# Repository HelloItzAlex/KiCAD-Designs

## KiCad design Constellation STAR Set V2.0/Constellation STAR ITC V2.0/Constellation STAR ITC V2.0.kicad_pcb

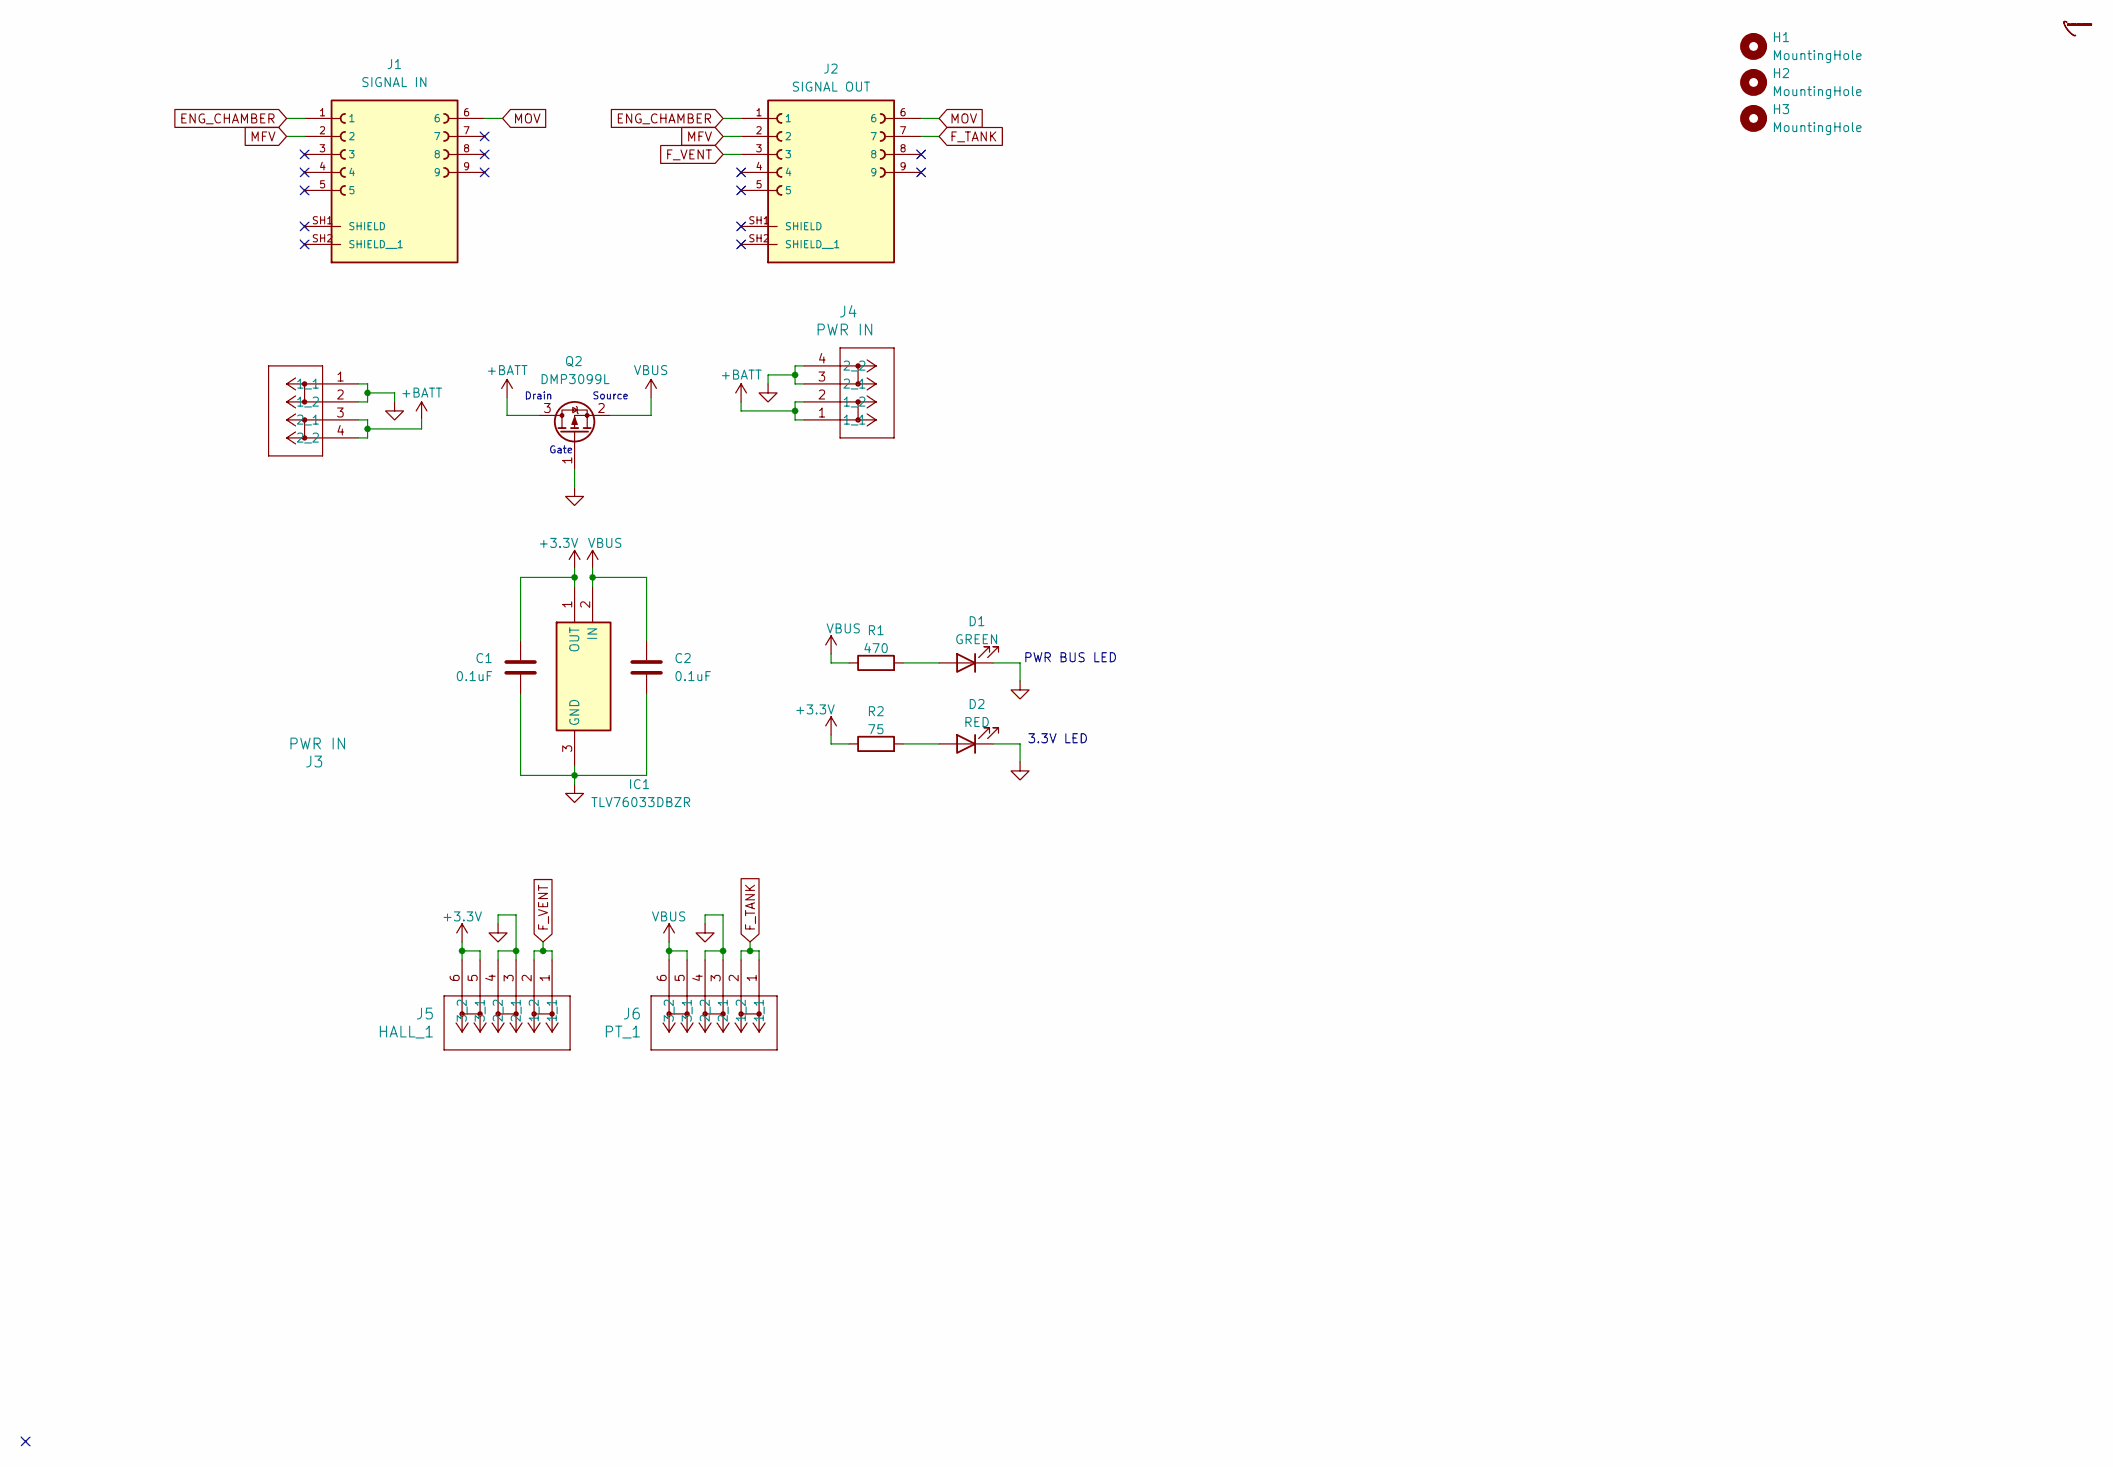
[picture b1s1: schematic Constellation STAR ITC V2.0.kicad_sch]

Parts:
C1, C2: 0.1uF; C_0805_2012Metric
D1: GREEN; LED_0805_2012Metric
D2: RED; LED_0805_2012Metric
H1, H2, H3: MountingHole; MountingHole_3.2mm_M3
IC1: TLV76033DBZR; SOT95P237X112-3N; Mouser Part Number 595-TLV76033DBZR
J1: SIGNAL IN; AMPHENOL_LD09S33E4GV00LF; PARTREV B
J2: SIGNAL OUT; AMPHENOL_LD09S33E4GV00LF; PARTREV B
J3, J4: PWR IN; CONN2_2601-1102_WAG
J5: HALL_1; CONN3_2601-1103_WAG
J6: PT_1; CONN3_2601-1103_WAG
Q2: DMP3099L; SOT-23-3
R1: 470; R_0805_2012Metric
R2: 75; R_0805_2012Metric

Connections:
+3.3V: C1.1, IC1.1 (OUT), J5.5 (3_1), J5.6 (3_2), R2.1
+BATT: J3.3 (2_1), J3.4 (2_2), J4.1 (1_1), J4.2 (1_2), Q2.3 (D)
ENG_CHAMBER: J1.1, J2.1
F_TANK: J2.7, J6.1 (1_1), J6.2 (1_2)
F_VENT: J2.3, J5.1 (1_1), J5.2 (1_2)
GND: C1.2, C2.2, D1.1 (K), D2.1 (K), IC1.3 (GND), J3.1 (1_1), J3.2 (1_2), J4.3 (2_1), J4.4 (2_2), J5.3 (2_1), J5.4 (2_2), J6.3 (2_1), J6.4 (2_2), Q2.1 (G)
MFV: J1.2, J2.2
MOV: J1.6, J2.6
unnamed: D1.2 (A), R1.2
unnamed: D2.2 (A), R2.2
VBUS: C2.1, IC1.2 (IN), J6.5 (3_1), J6.6 (3_2), Q2.2 (S), R1.1

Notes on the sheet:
PWR BUS LED
Source
Gate
Drain
3.3V LED

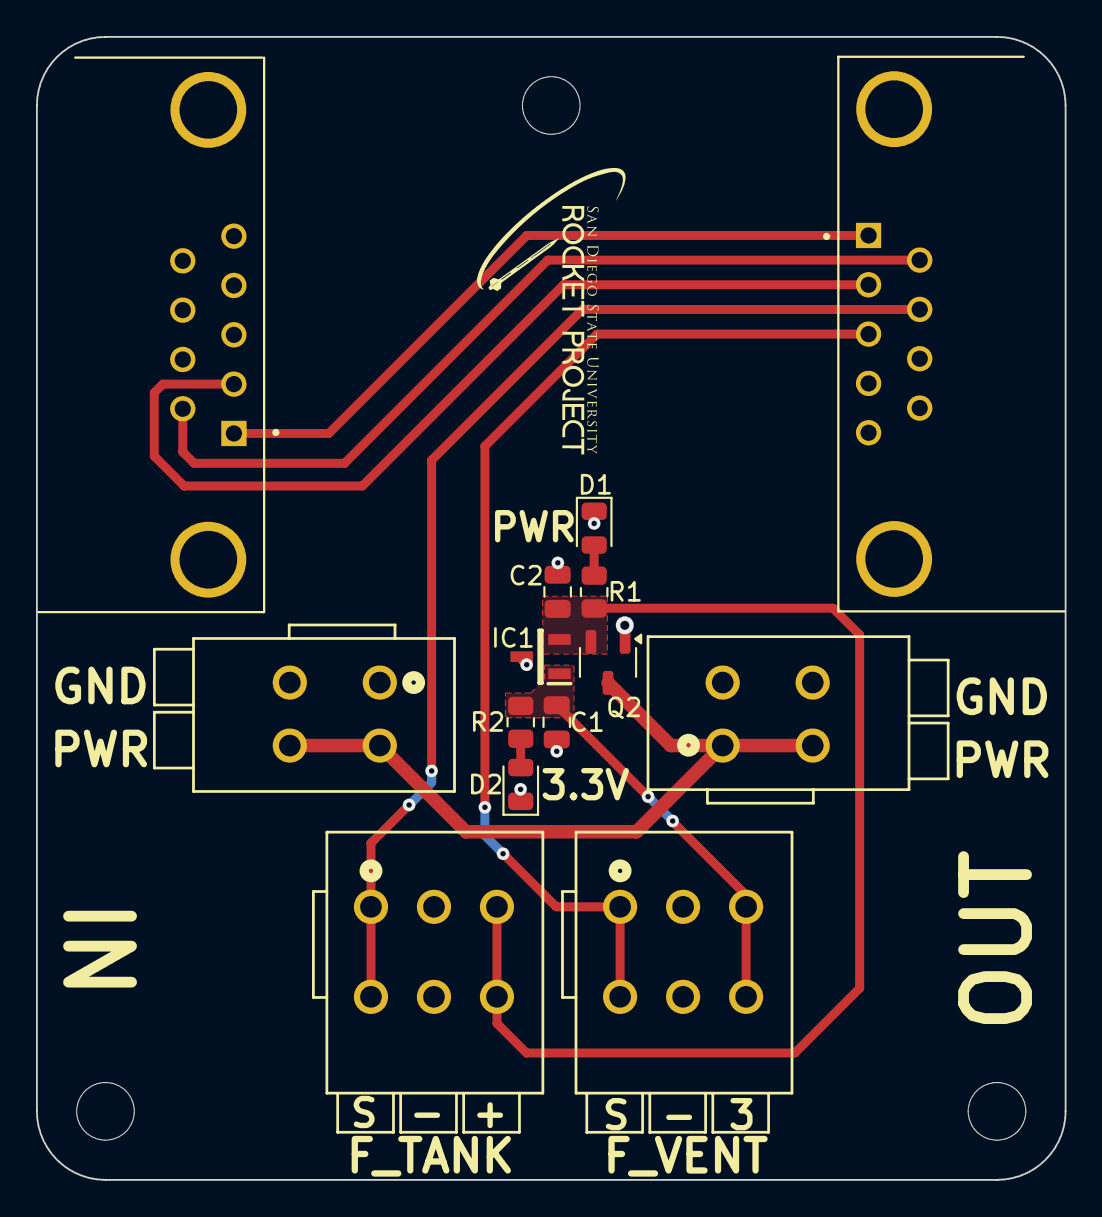
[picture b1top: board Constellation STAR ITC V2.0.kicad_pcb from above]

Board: 2 copper layers, 57.1 x 63.5 mm, 17 parts (0 on the bottom side), 11 nets.

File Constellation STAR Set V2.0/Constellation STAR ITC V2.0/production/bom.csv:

Designator,Footprint,Quantity,Value,LCSC Part #
"C1, C2",0805,2,0.1uF,
D1,0805,1,GREEN,
D2,0805,1,RED,
IC1,SOT95P237X112-3N,1,TLV76033DBZR,
J1,AMPHENOL_LD09S33E4GV00LF,1,SIGNAL IN,
J2,AMPHENOL_LD09S33E4GV00LF,1,SIGNAL OUT,
"J3, J4",CONN2_2601-1102_WAG,2,PWR IN,
J5,CONN3_2601-1103_WAG,1,HALL_1,
J6,CONN3_2601-1103_WAG,1,PT_1,
Q2,SOT-23-3,1,DMP3099L,
R1,0805,1,470,
R2,0805,1,75,

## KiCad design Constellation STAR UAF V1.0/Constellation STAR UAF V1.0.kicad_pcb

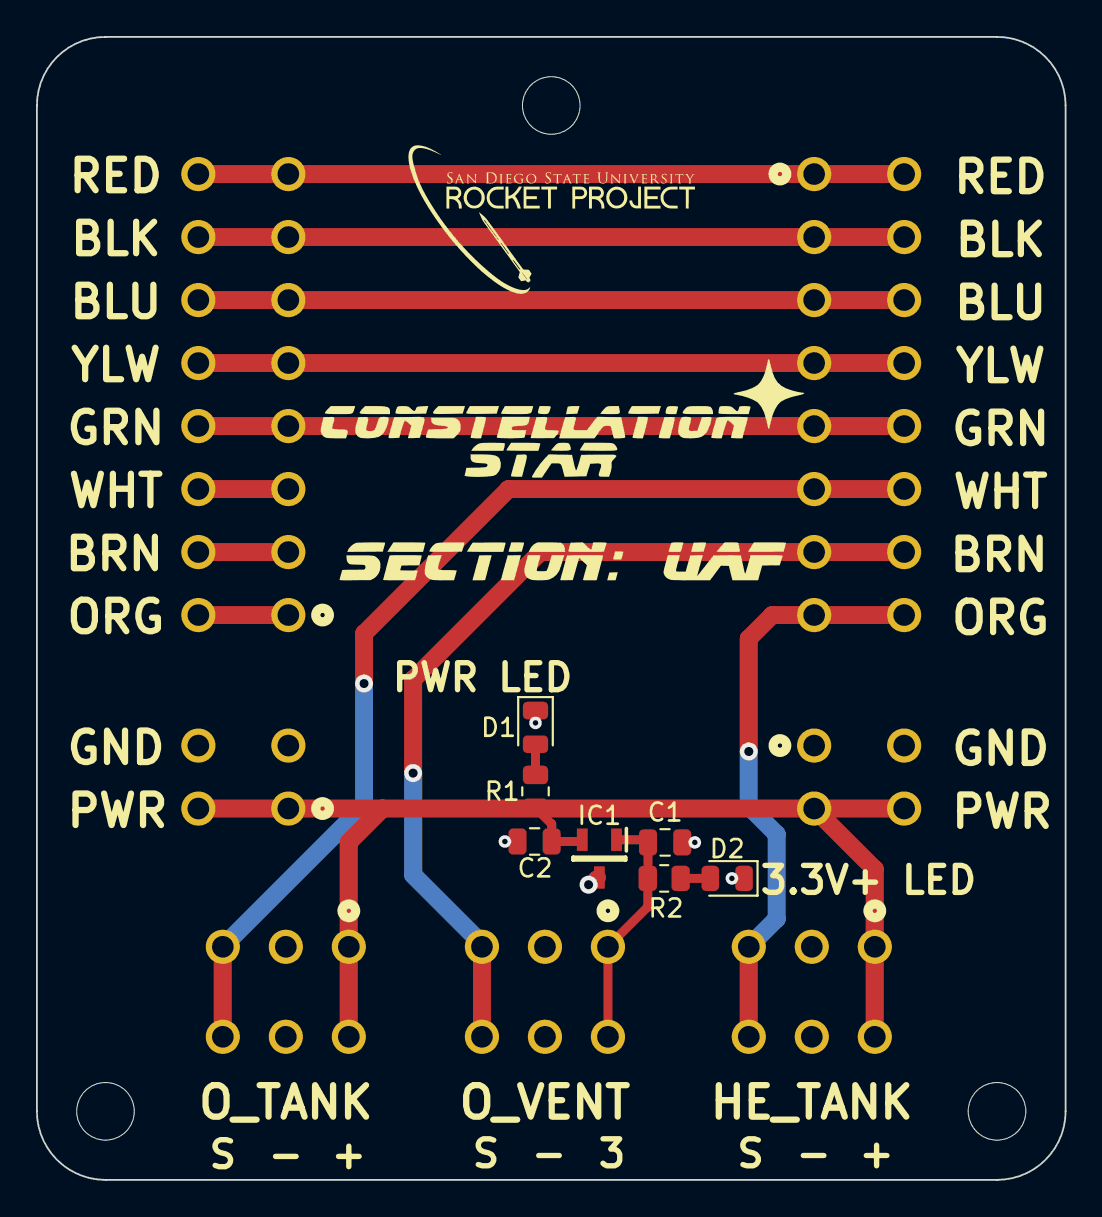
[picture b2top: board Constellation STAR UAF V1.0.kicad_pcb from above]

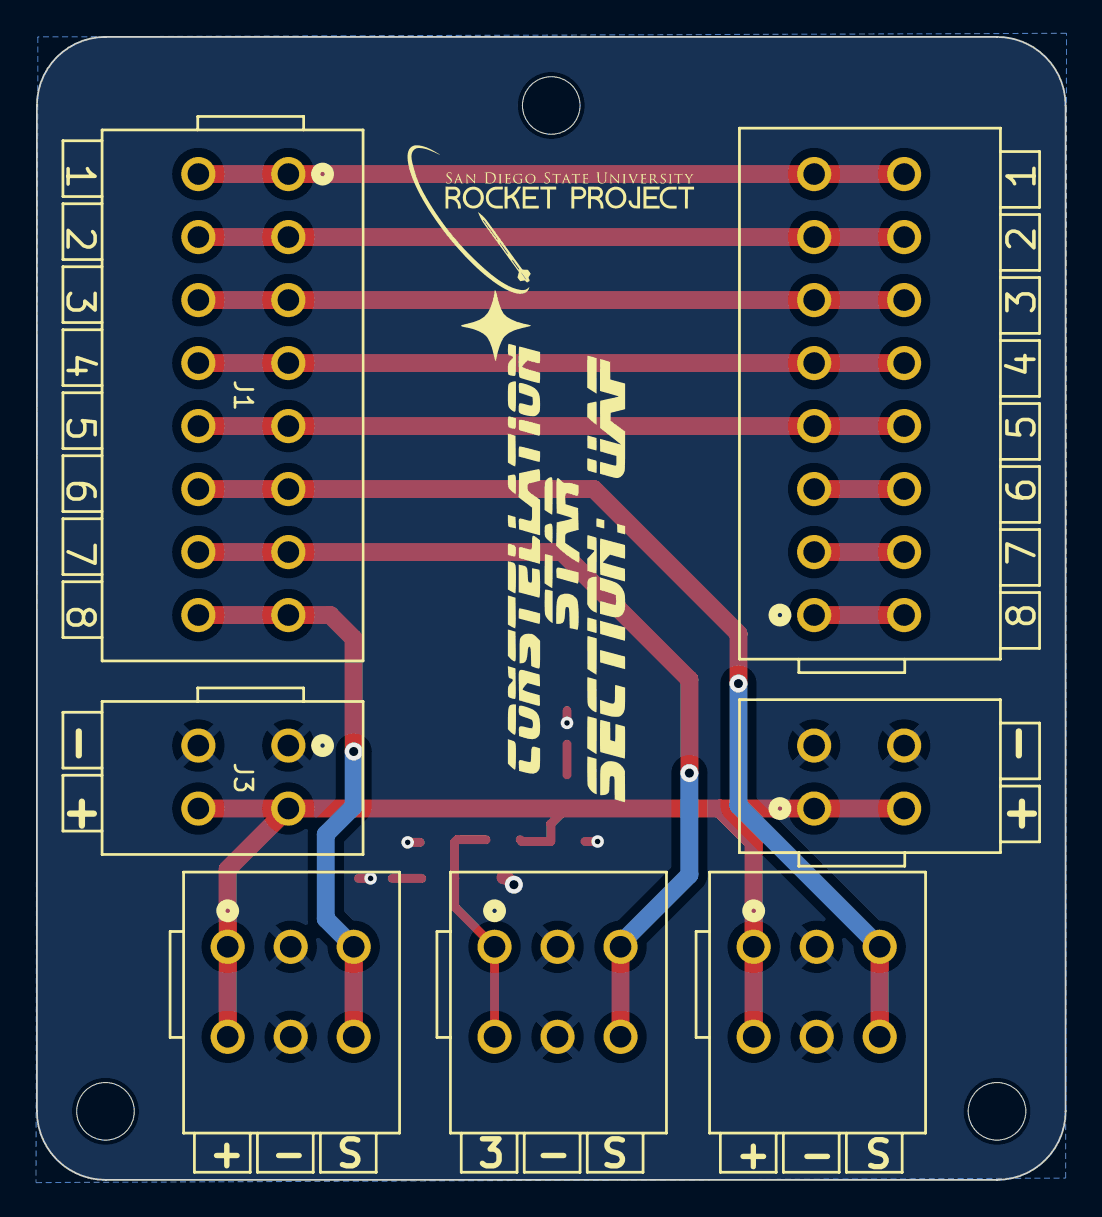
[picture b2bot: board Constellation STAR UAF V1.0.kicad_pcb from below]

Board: 2 copper layers, 57.1 x 63.5 mm, 17 parts (7 on the bottom side), 13 nets.

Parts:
C1, C2: 0.1uF; C_0805_2012Metric
D1, D2: RED; LED_0805_2012Metric
H1, H2, H3: MountingHole; MountingHole_3.2mm_M3
IC1: TLV76033DBZR; SOT95P237X112-3N
J1, J2: SIGNAL_OUT; CONN8_2601-1108_WAG
J3, J4: PWR IN; CONN2_2601-1102_WAG
J5: HALL_1; CONN3_2601-1103_WAG
J6: PT_1; CONN3_2601-1103_WAG
J7: PT_2; CONN3_2601-1103_WAG
R1, R2: R; R_0805_2012Metric

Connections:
+3.3V: C1.1, IC1.1 (OUT), J5.1 (1_1), J5.2 (1_2), R2.1
ENG_CHAMBER: J1.1 (1_1), J1.2 (1_2), J2.15 (8_1), J2.16 (8_2)
F_TANK: J1.7 (4_1), J1.8 (4_2), J2.9 (5_1), J2.10 (5_2)
F_VENT: J1.9 (5_1), J1.10 (5_2), J2.7 (4_1), J2.8 (4_2)
GND: C1.2, C2.2, D1.1 (K), D2.1 (K), IC1.3 (GND), J3.1 (1_1), J3.2 (1_2), J4.3 (2_1), J4.4 (2_2), J5.3 (2_1), J5.4 (2_2), J6.3 (2_1), J6.4 (2_2), J7.3 (2_1), J7.4 (2_2)
HE_TANK: J1.15 (8_1), J1.16 (8_2), J7.5 (3_1), J7.6 (3_2)
MFV: J1.5 (3_1), J1.6 (3_2), J2.11 (6_1), J2.12 (6_2)
MOV: J1.3 (2_1), J1.4 (2_2), J2.13 (7_1), J2.14 (7_2)
unnamed: D1.2 (A), R1.2
unnamed: D2.2 (A), R2.2
O_TANK: J1.11 (6_1), J1.12 (6_2), J6.5 (3_1), J6.6 (3_2)
O_VENT: J1.13 (7_1), J1.14 (7_2), J5.5 (3_1), J5.6 (3_2)
VBUS: C2.1, IC1.2 (IN), J3.3 (2_1), J3.4 (2_2), J4.1 (1_1), J4.2 (1_2), J6.1 (1_1), J6.2 (1_2), J7.1 (1_1), J7.2 (1_2), R1.1

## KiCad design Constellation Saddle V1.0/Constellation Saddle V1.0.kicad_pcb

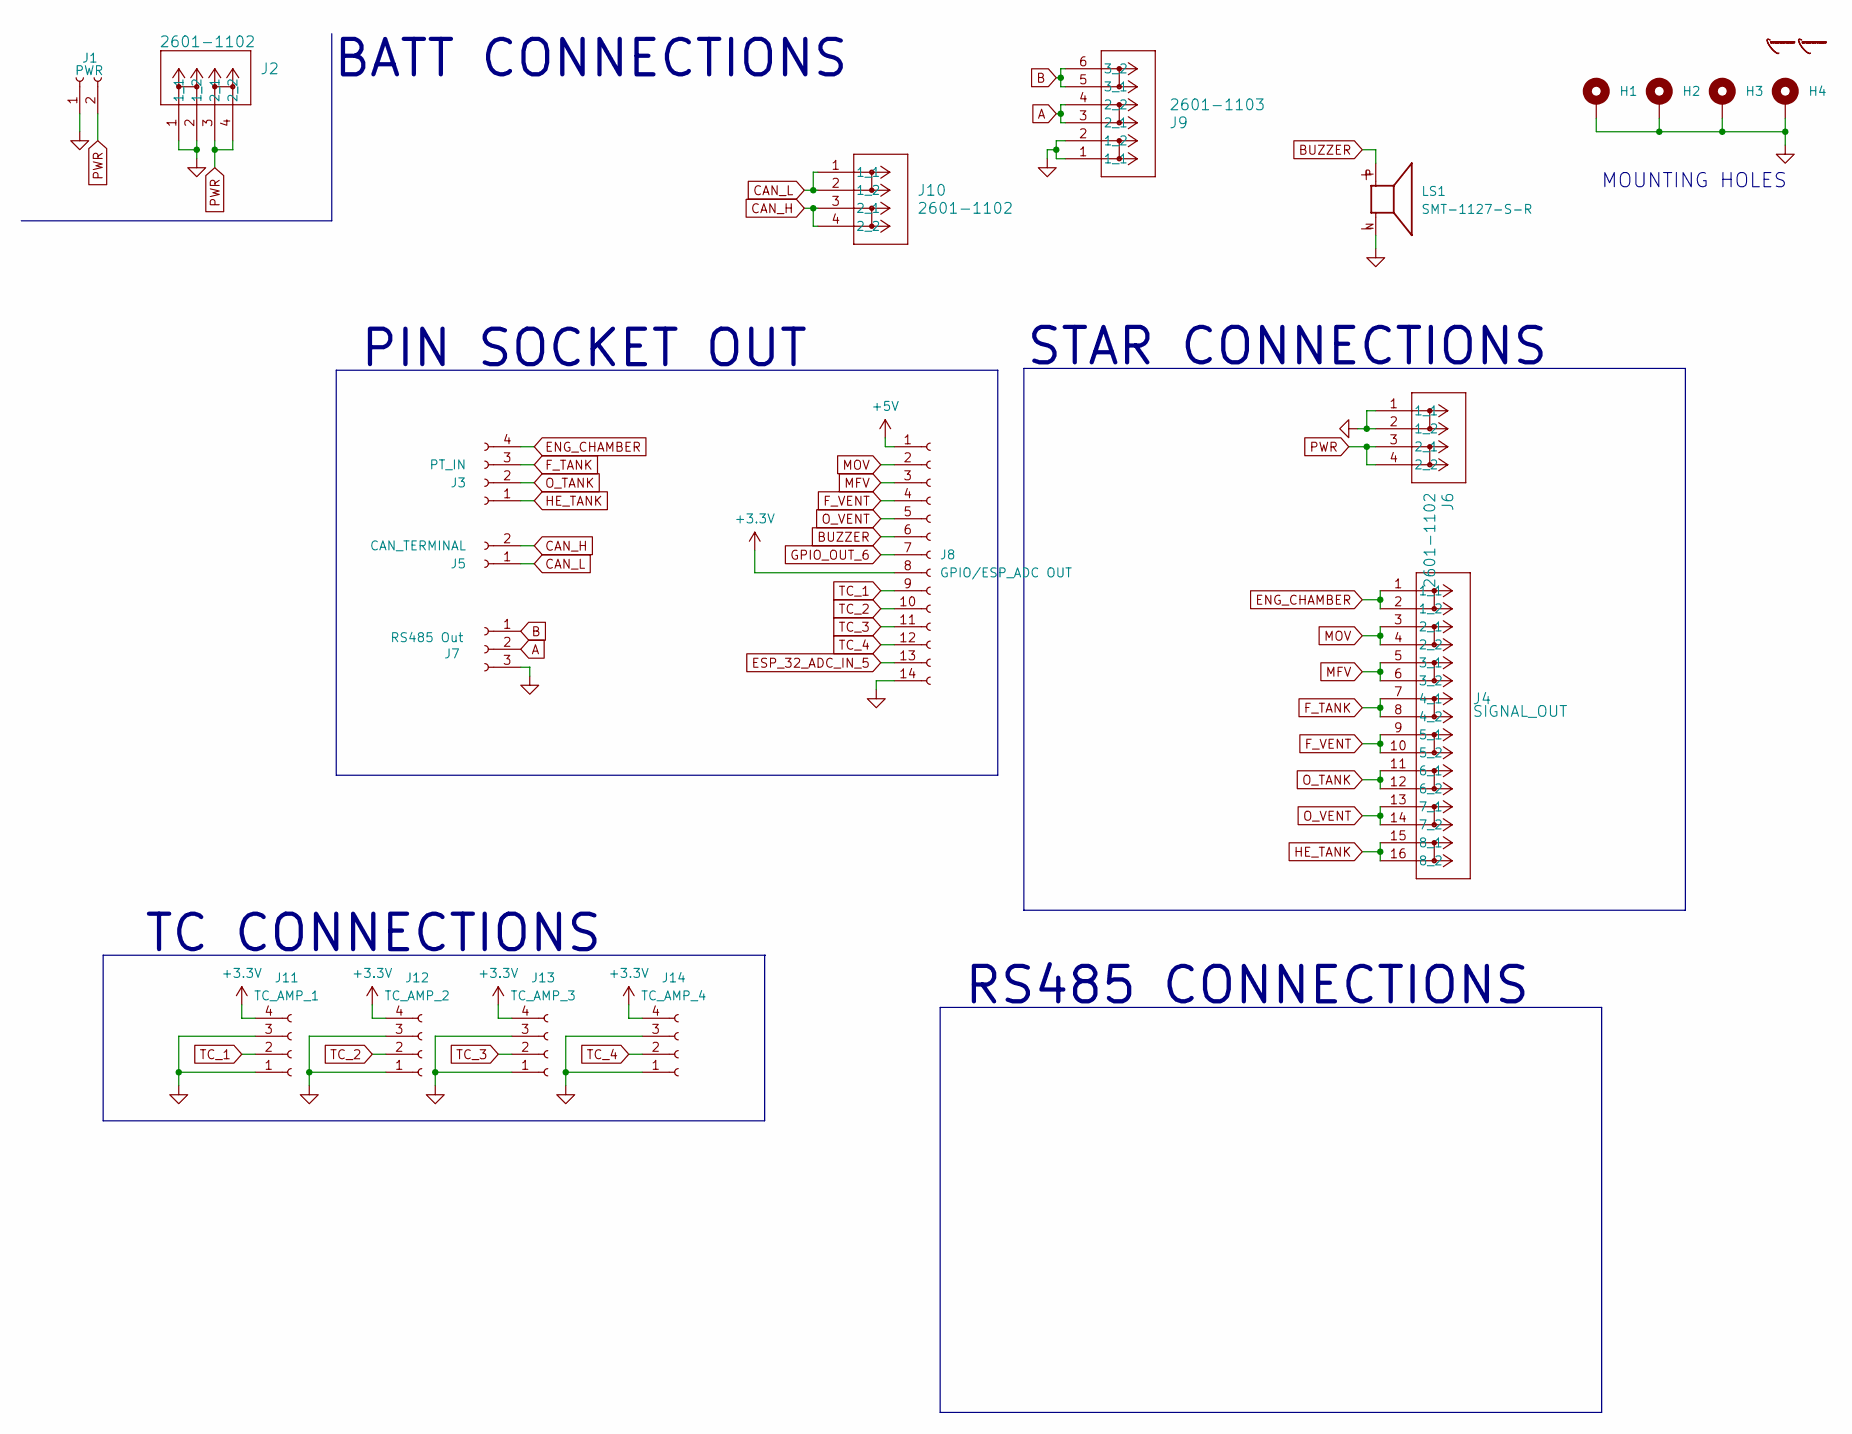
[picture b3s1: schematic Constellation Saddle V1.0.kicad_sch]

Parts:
H1, H2, H3, H4: MountingHole_Pad; MountingHole_3.2mm_M3_DIN965_Pad
J1: PWR; PinSocket_1x02_P2.54mm_Vertical
J2, J6, J10: 2601-1102; CONN2_2601-1102_WAG
J3: PT_IN; PinSocket_1x04_P2.54mm_Vertical
J4: SIGNAL_OUT; CONN8_2601-1108_WAG
J5: CAN_TERMINAL; PinSocket_1x02_P2.54mm_Vertical
J7: RS485 Out; PinSocket_1x03_P2.54mm_Vertical
J8: GPIO/ESP_ADC OUT; PinSocket_1x14_P2.54mm_Vertical
J9: 2601-1103; CONN3_2601-1103_WAG
J11: TC_AMP_1; PinSocket_1x04_P2.54mm_Vertical
J12: TC_AMP_2; PinSocket_1x04_P2.54mm_Vertical
J13: TC_AMP_3; PinSocket_1x04_P2.54mm_Vertical
J14: TC_AMP_4; PinSocket_1x04_P2.54mm_Vertical
LS1: SMT-1127-S-R; XDCR_SMT-1127-S-R; PARTREV 2014/08/05

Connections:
+3.3V: J8.8, J11.4, J12.4, J13.4, J14.4
+5V: J8.1
A: J7.2, J9.3 (2_1), J9.4 (2_2)
B: J7.1, J9.5 (3_1), J9.6 (3_2)
BUZZER: J8.6, LS1.P
CAN_H: J5.2, J10.3 (2_1), J10.4 (2_2)
CAN_L: J5.1, J10.1 (1_1), J10.2 (1_2)
ENG_CHAMBER: J3.4, J4.1 (1_1), J4.2 (1_2)
ESP_32_ADC_IN_5: J8.13
F_TANK: J3.3, J4.7 (4_1), J4.8 (4_2)
F_VENT: J4.9 (5_1), J4.10 (5_2), J8.4
GND: H1.1, H2.1, H3.1, H4.1, J1.1, J2.1 (1_1), J2.2 (1_2), J6.1 (1_1), J6.2 (1_2), J7.3, J8.14, J9.1 (1_1), J9.2 (1_2), J11.1, J11.3, J12.1, J12.3, J13.1, J13.3, J14.1, J14.3, LS1.N
GPIO_OUT_6: J8.7
HE_TANK: J3.1, J4.15 (8_1), J4.16 (8_2)
MFV: J4.5 (3_1), J4.6 (3_2), J8.3
MOV: J4.3 (2_1), J4.4 (2_2), J8.2
O_TANK: J3.2, J4.11 (6_1), J4.12 (6_2)
O_VENT: J4.13 (7_1), J4.14 (7_2), J8.5
PWR: J1.2, J2.3 (2_1), J2.4 (2_2), J6.3 (2_1), J6.4 (2_2)
TC_1: J8.9, J11.2
TC_2: J8.10, J12.2
TC_3: J8.11, J13.2
TC_4: J8.12, J14.2

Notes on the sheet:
MOUNTING HOLES
BATT CONNECTIONS
STAR CONNECTIONS
TC CONNECTIONS
PIN SOCKET OUT
RS485 CONNECTIONS

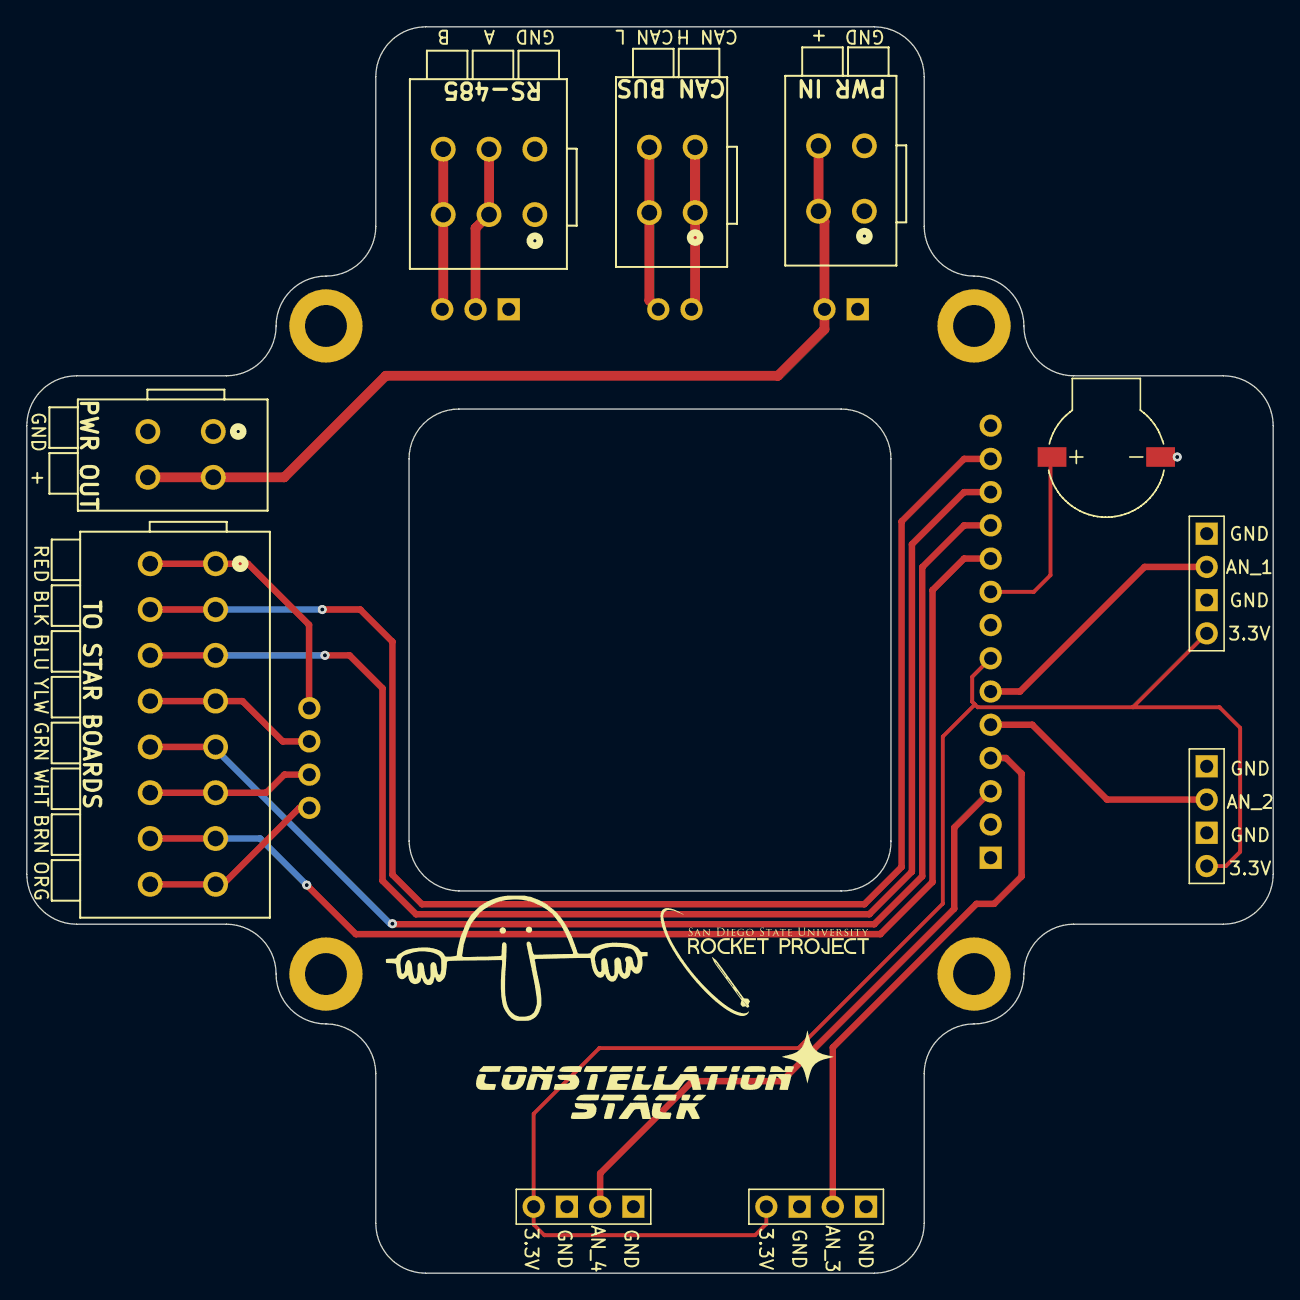
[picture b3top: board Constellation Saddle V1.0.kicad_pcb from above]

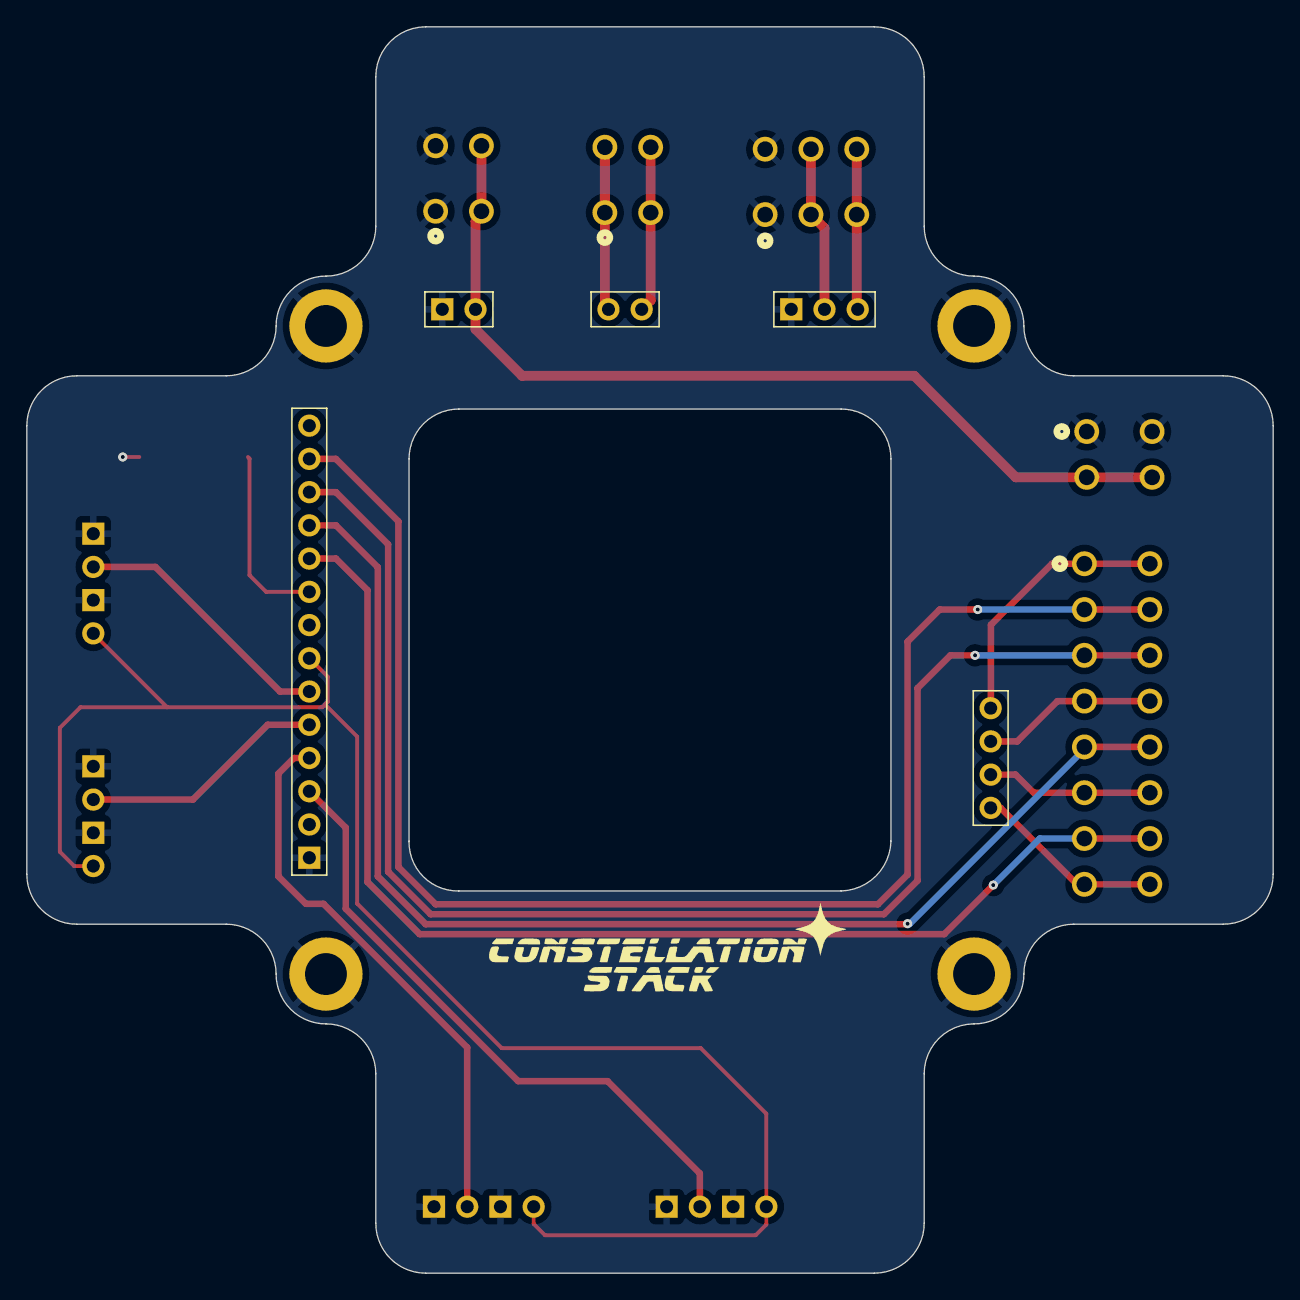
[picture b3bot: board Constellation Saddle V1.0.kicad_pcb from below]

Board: 2 copper layers, 95.2 x 95.2 mm, 19 parts (5 on the bottom side), 20 nets.

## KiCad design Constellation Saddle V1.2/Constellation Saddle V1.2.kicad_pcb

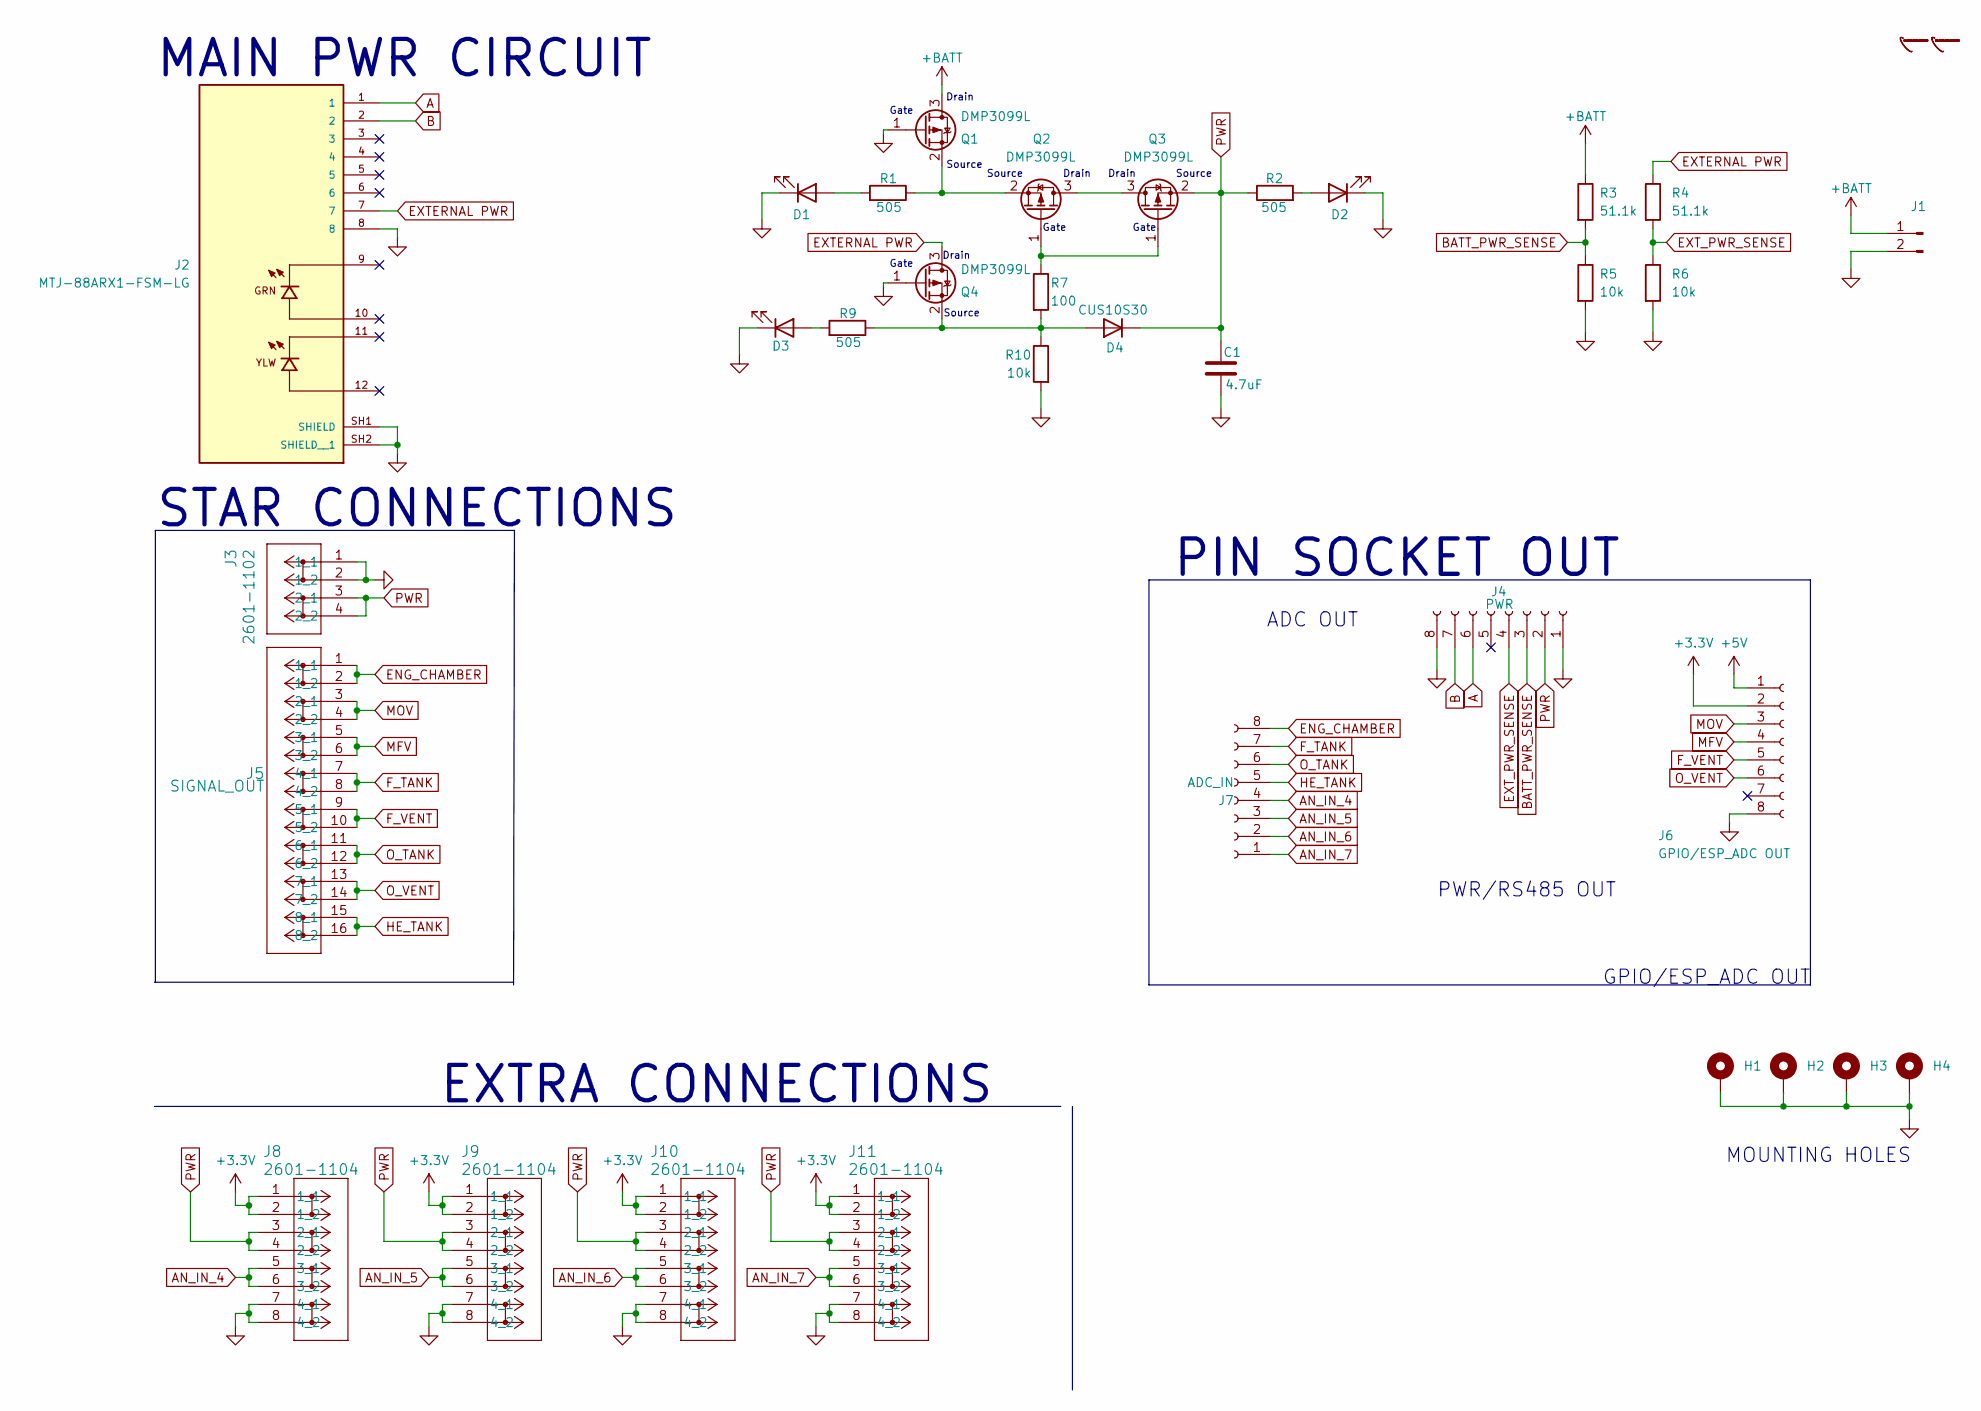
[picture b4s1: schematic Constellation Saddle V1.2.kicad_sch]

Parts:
C1: 4.7uF; C_0805_2012Metric
D1, D2, D3: LED; LED_0805_2012Metric
D4: CUS10S30; D_SOD-323
H1, H2, H3, H4: MountingHole_Pad; MountingHole_3.2mm_M3_DIN965_Pad
J1: Conn_01x02_Pin; SolderWire-0.75sqmm_1x02_P4.8mm_D1.25mm_OD2.3mm_Relief
J2: MTJ-88ARX1-FSM-LG; ADAMTECH_MTJ-88ARX1-FSM-LG; PARTREV H
J3: 2601-1102; CONN2_2601-1102_WAG
J4: PWR; PinSocket_1x08_P2.54mm_Vertical
J5: SIGNAL_OUT; CONN8_2601-1108_WAG
J6: GPIO/ESP_ADC OUT; PinSocket_1x08_P2.54mm_Vertical
J7: ADC_IN; PinSocket_1x08_P2.54mm_Vertical
J8, J9, J10, J11: 2601-1104; CONN4_2601-1104_WAG
Q1, Q2, Q3, Q4: DMP3099L; SOT-23-3
R1, R2, R9: 505; R_0805_2012Metric
R3, R4: 51.1k; R_0805_2012Metric
R5, R6, R10: 10k; R_0805_2012Metric
R7: 100; R_0805_2012Metric

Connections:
+3.3V: J6.2, J8.1 (1_1), J8.2 (1_2), J9.1 (1_1), J9.2 (1_2), J10.1 (1_1), J10.2 (1_2), J11.1 (1_1), J11.2 (1_2)
+5V: J6.1
+BATT: J1.1, Q1.3 (D), R3.1
A: J2.1, J4.6
AN_IN_4: J7.4, J8.5 (3_1), J8.6 (3_2)
AN_IN_5: J7.3, J9.5 (3_1), J9.6 (3_2)
AN_IN_6: J7.2, J10.5 (3_1), J10.6 (3_2)
AN_IN_7: J7.1, J11.5 (3_1), J11.6 (3_2)
B: J2.2, J4.7
BATT_PWR_SENSE: J4.3, R3.2, R5.1
ENG_CHAMBER: J5.1 (1_1), J5.2 (1_2), J7.8
EXTERNAL PWR: J2.7, Q4.3 (D), R4.1
EXT_PWR_SENSE: J4.4, R4.2, R6.1
F_TANK: J5.7 (4_1), J5.8 (4_2), J7.7
F_VENT: J5.9 (5_1), J5.10 (5_2), J6.5
GND: C1.2, D1.1 (K), D2.1 (K), D3.1 (K), H1.1, H2.1, H3.1, H4.1, J1.2, J2.8, J2.SH1 (SHIELD), J2.SH2 (SHIELD__1), J3.1 (1_1), J3.2 (1_2), J4.1, J4.8, J6.8, J8.7 (4_1), J8.8 (4_2), J9.7 (4_1), J9.8 (4_2), J10.7 (4_1), J10.8 (4_2), J11.7 (4_1), J11.8 (4_2), Q1.1 (G), Q4.1 (G), R5.2, R6.2, R10.2
HE_TANK: J5.15 (8_1), J5.16 (8_2), J7.5
MFV: J5.5 (3_1), J5.6 (3_2), J6.4
MOV: J5.3 (2_1), J5.4 (2_2), J6.3
unnamed: D1.2 (A), R1.2
unnamed: D2.2 (A), R2.2
unnamed: D3.2 (A), R9.2
unnamed: D4.2 (A), Q4.2 (S), R7.2, R9.1, R10.1
unnamed: Q1.2 (S), Q2.2 (S), R1.1
unnamed: Q2.3 (D), Q3.3 (D)
unnamed: Q2.1 (G), Q3.1 (G), R7.1
O_TANK: J5.11 (6_1), J5.12 (6_2), J7.6
O_VENT: J5.13 (7_1), J5.14 (7_2), J6.6
PWR: C1.1, D4.1 (K), J3.3 (2_1), J3.4 (2_2), J4.2, J8.3 (2_1), J8.4 (2_2), J9.3 (2_1), J9.4 (2_2), J10.3 (2_1), J10.4 (2_2), J11.3 (2_1), J11.4 (2_2), Q3.2 (S), R2.1

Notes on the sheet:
Gate
GPIO/ESP_ADC OUT
Drain
Source
MOUNTING HOLES
PWR/RS485 OUT
MAIN PWR CIRCUIT
ADC OUT
STAR CONNECTIONS
EXTRA CONNECTIONS
PIN SOCKET OUT

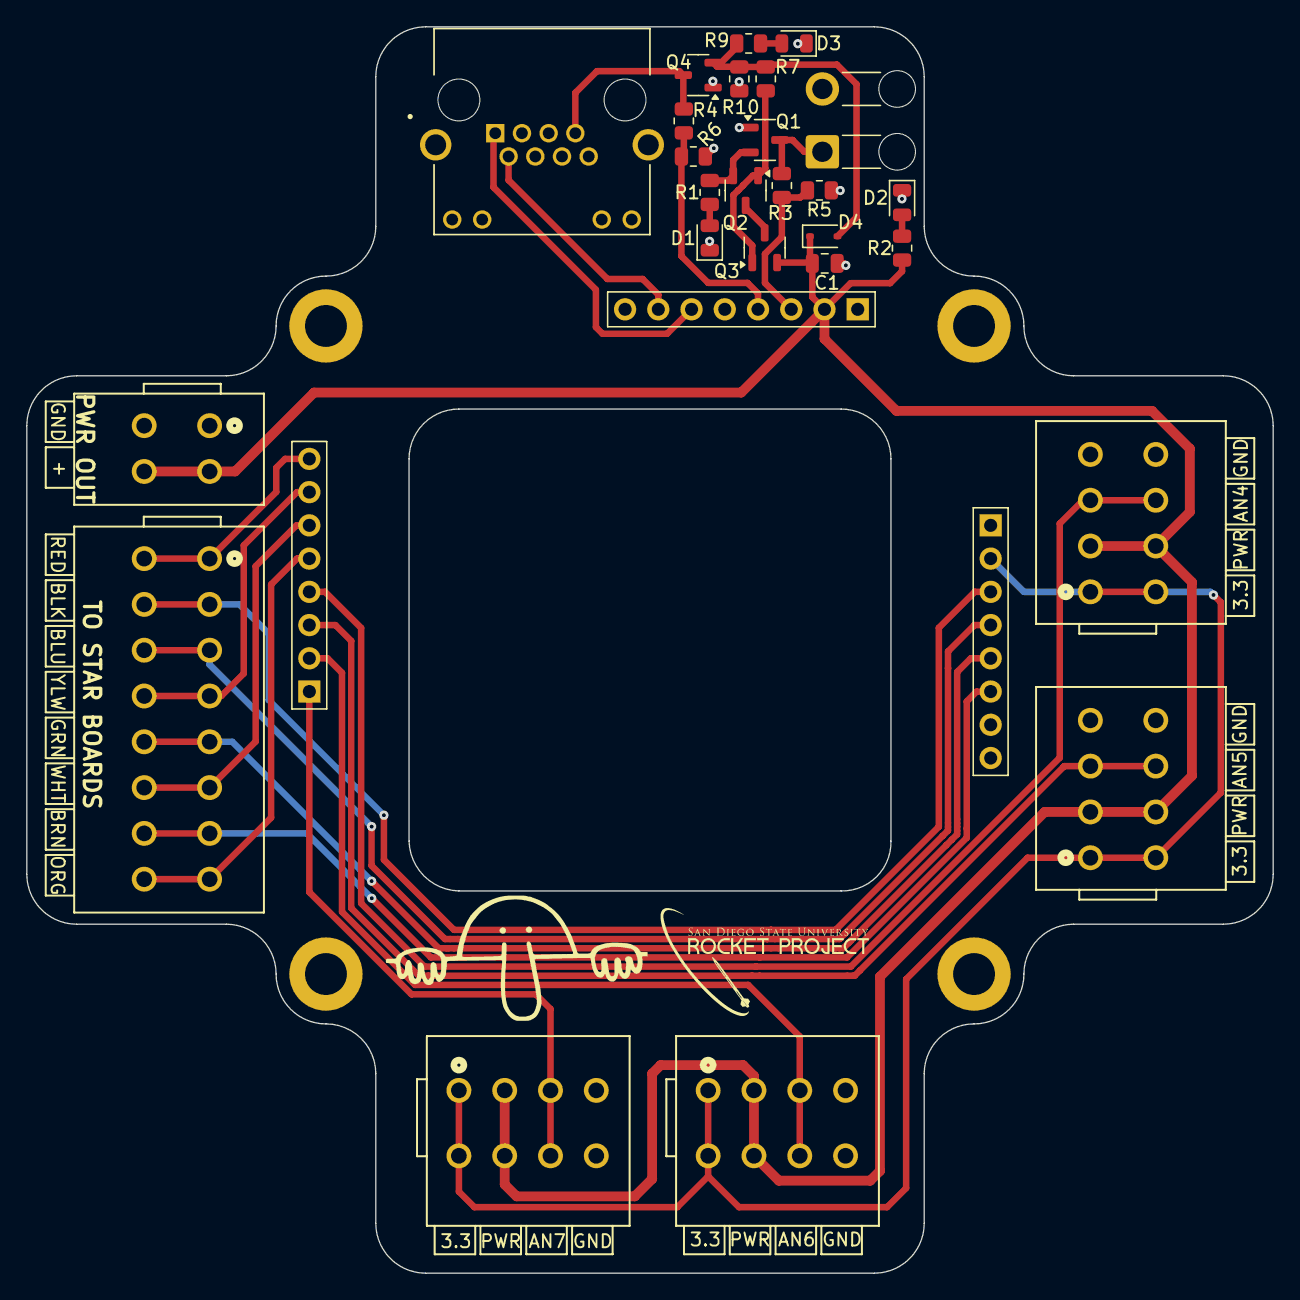
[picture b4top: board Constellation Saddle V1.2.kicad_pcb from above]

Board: 2 copper layers, 95.2 x 95.2 mm, 33 parts (0 on the bottom side), 28 nets.

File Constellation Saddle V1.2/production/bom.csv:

Designator,Footprint,Quantity,Value,LCSC Part #
C1,0805,1,4.7uF,
"D1, D2, D3",0805,3,LED,
D4,D_SOD-323,1,CUS10S30,
"H1, H2, H3, H4",MountingHole_3.2mm_M3_DIN965_Pad,4,MountingHole_Pad,
J1,SolderWire-0.75sqmm_1x02_P4.8mm_D1.25mm_OD2.3mm_Relief,1,Conn_01x02_Pin,
"J10, J11, J8, J9",CONN4_2601-1104_WAG,4,2601-1104,
J2,ADAMTECH_MTJ-88ARX1-FSM-LG,1,MTJ-88ARX1-FSM-LG,
J3,CONN2_2601-1102_WAG,1,2601-1102,
J4,PinSocket_1x08_P2.54mm_Vertical,1,PWR,
J5,CONN8_2601-1108_WAG,1,SIGNAL_OUT,
J6,PinSocket_1x08_P2.54mm_Vertical,1,GPIO/ESP_ADC OUT,
J7,PinSocket_1x08_P2.54mm_Vertical,1,ADC_IN,
"Q1, Q2, Q3, Q4",SOT-23-3,4,DMP3099L,
"R1, R2, R9",0805,3,505,
"R10, R5, R6",0805,3,10k,
"R3, R4",0805,2,51.1k,
R7,0805,1,100,
